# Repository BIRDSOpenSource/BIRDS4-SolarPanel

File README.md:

<div align="center">
  
</div>

# BIRDS4-SolarPanel
 Documentation for the Solar Panel Boards used in the BIRDS4 Satellite

## About the BIRDS4 Program:

The Mission Statement of the Project is:

> “By successfully building and operating first satellite of nation, advance toward indigenous space program in each country”

The project is led by Kyushu Institute of Technology in Japan and involves students from Philippines, Paraguay, Nepal, Turkey and Japan.

Satellite Names: Tsuru (Japan), Guarani-1 (Paraguay) and Maya-2 (Phillipines)

Stakeholders:  Paraguayan Space Agency, Polytechnic Faculty of National University of Asuncion, and Kyushu Institute of Technology (Kyutech) for Japan.

Project duration: 2018-2022

CubeSat: 1U (10x10x10) cm3

Weight: 1.13kg

Launch Date: 21st February 2021 

BIRDS-4 has 1 main missions in total; APRS Store and forward mission

## Organisation structure

```bash

├── .gitattributes
├── LICENSE
├── README.md
└── Solar panel
    ├── +X
    │   ├── B4_FM_+X_SOLAR_PANEL_v2.brd
    │   └── B4_FM_+X_SOLAR_PANEL_v2.sch
    ├── +Y
    │   ├── B4_FM_+Y_SOLAR_PANEL.brd
    │   └── B4_FM_+Y_SOLAR_PANEL.sch
    ├── +Z
    │   ├── B4_FM_+Z_SOLAR_PANEL.brd
    │   └── B4_FM_+Z_SOLAR_PANEL.sch
    ├── -X
    │   ├── B4_FM_-X_SOLAR_PANEL_v2.brd
    │   └── B4_FM_-X_SOLAR_PANEL_v2.sch
    ├── -Z
    │   ├── B4_FM_-Z_SOLAR_PANEL.brd
    │   └── B4_FM_-Z_SOLAR_PANEL.sch
    └── B4_FM_solar_panel_List_20190923.xlsx
```

> [!CAUTION]
> The files `.sch` and `.brd` files in this repositiry were created using Eagle software.
 
For those that want to import these files into 
KiCAD7 [here's how you do it](https://community.element14.com/technologies/open-source-hardware/b/blog/posts/working-with-kicad-7-importing-eagle-files) 
 or KiCAD5.1 [here's how you do it](https://www.youtube.com/watch?v=RBc02MwpKxk&t=1s).
## Features

## I like this project, can I help you?
You are welcome 🙂

* Give us a star ⭐
* Watch repository to be notified about updates 👀
* If you will find some errors, report them in Issues 🐞
* Try Birds designs on some real computer and let us know how it worked in Discussions. 💬
* We would greatly appreciate if you would also tell others about this ecosystem, it helps us to improve BIRDS Open Source. Thank you!

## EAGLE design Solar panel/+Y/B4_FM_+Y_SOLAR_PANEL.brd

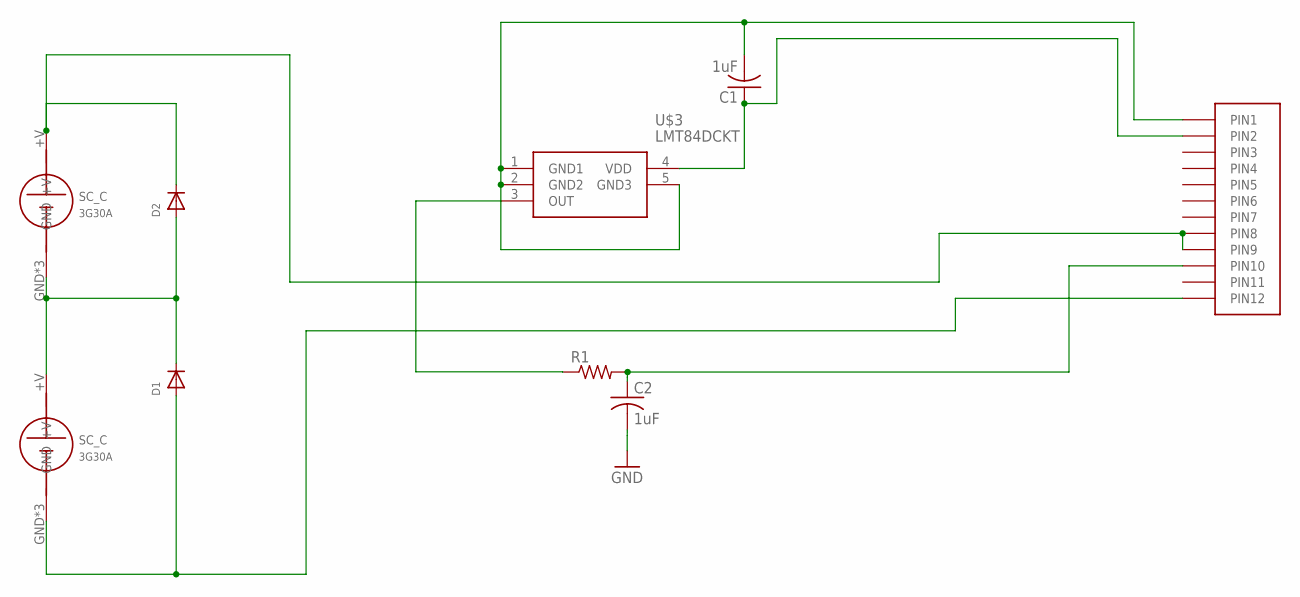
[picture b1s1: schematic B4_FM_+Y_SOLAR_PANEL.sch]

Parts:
C1, C2: 1uF; C0805
D1, D2: DIODE_SOD-123FL; SOD-123FL
R1: R-US_R0402; R0402
U$1: HEADER12PIN
U$3: LMT84DCKT; SOT65P210X110-5N
U$4, U$5: SC_C

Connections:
+V: D2.C, U$1.P8 (PIN8), U$1.P9 (PIN9), U$4.+V
GND: C1.2, C2.2, D1.A, U$1.P1 (PIN1), U$1.P12 (PIN12), U$3.1 (GND1), U$3.2 (GND2), U$3.5 (GND3), U$5.GND, U$5.GND1 (GND), U$5.GND2 (GND)
unnamed: D1.C, D2.A, U$4.GND, U$4.GND1 (GND), U$4.GND2 (GND), U$5.+V
unnamed: R1.1, U$3.3 (OUT)
unnamed: C2.1, R1.2, U$1.P10 (PIN10)
unnamed: C1.1, U$1.P2 (PIN2), U$3.4 (VDD)

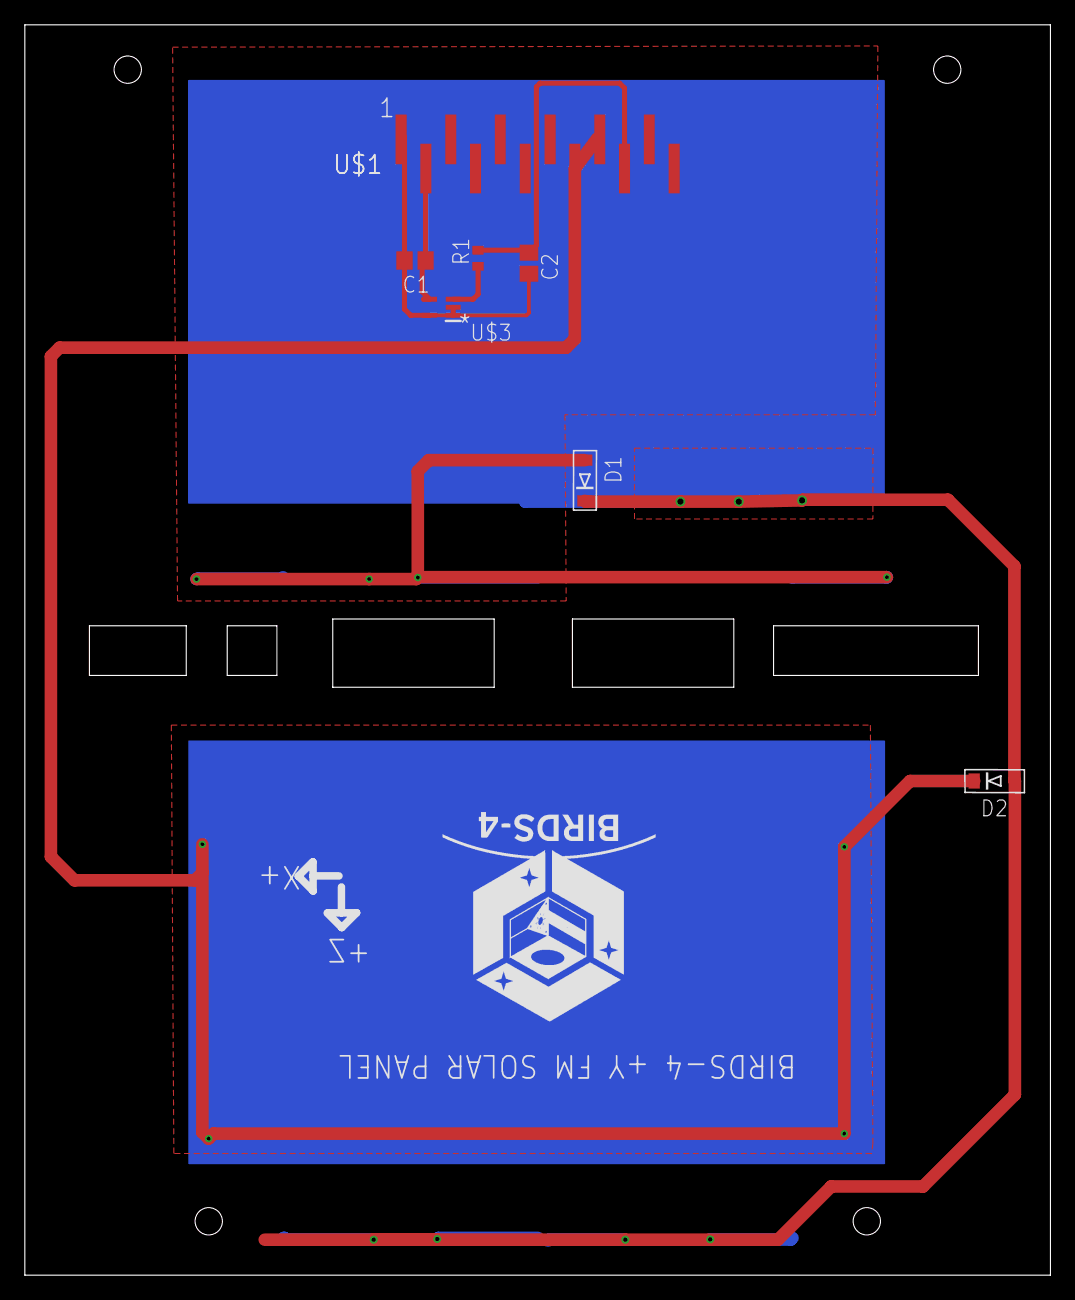
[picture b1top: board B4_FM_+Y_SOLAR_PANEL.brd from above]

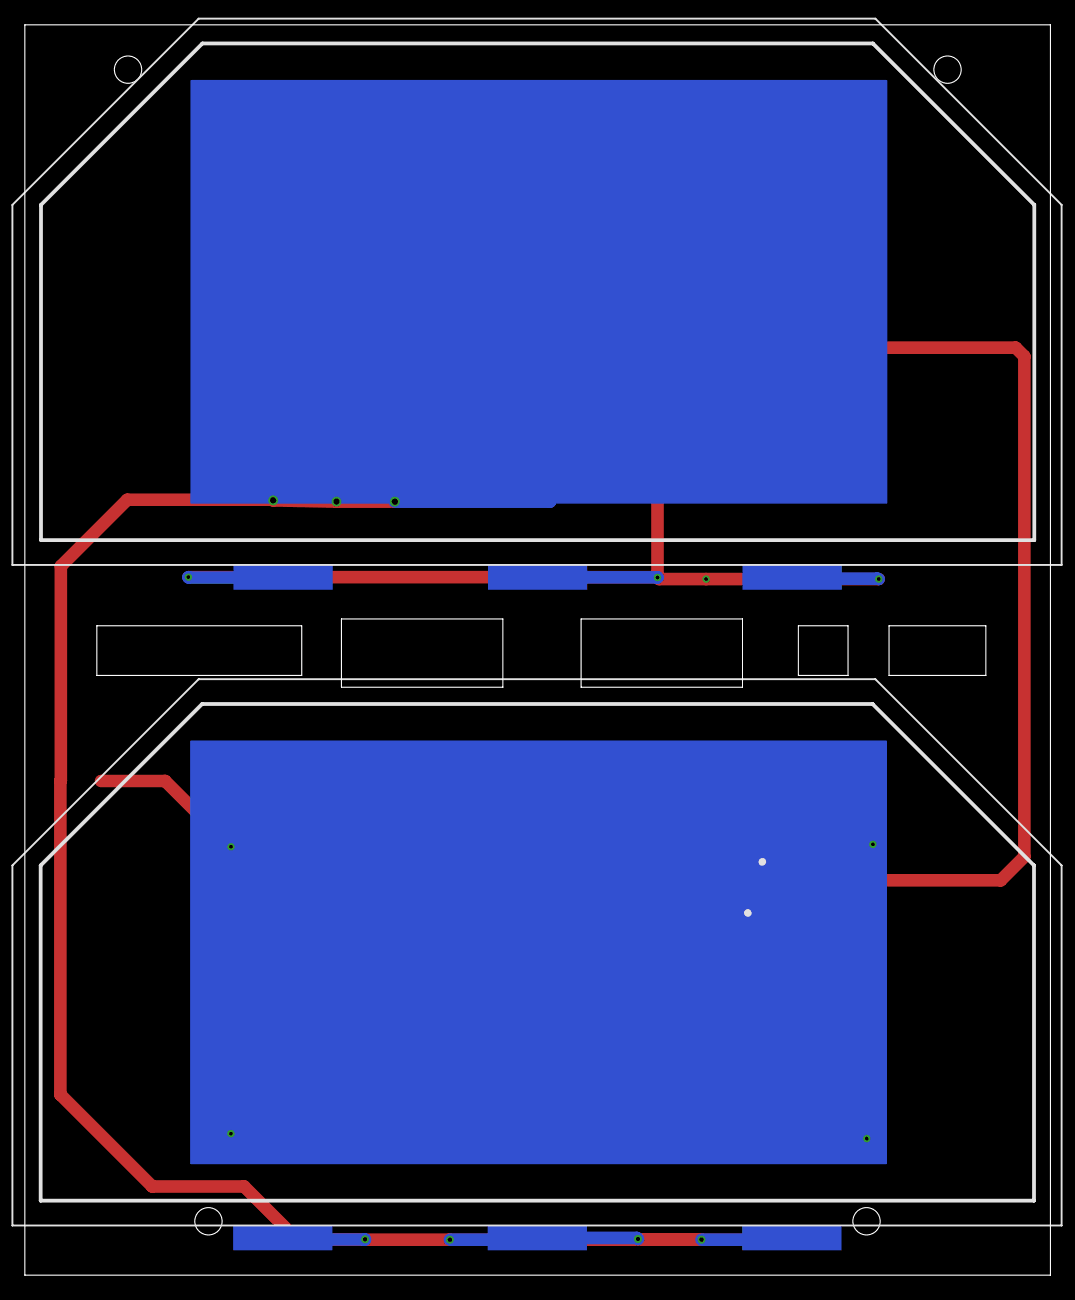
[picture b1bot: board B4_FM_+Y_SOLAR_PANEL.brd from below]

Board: 2 copper layers, 82.6 x 100.7 mm, 9 parts (2 on the bottom side), 6 nets.
